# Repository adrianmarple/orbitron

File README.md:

# Basics

Lumatron is a LED sculpture system. You are free to play with this code, but as per the license you may not make money from it.

## TL;DR
```
       ┌──────────────┐  ┌──────────────┐  ┌──────────────┐
       │  Controller  │  │    Admin     │  │   Emulator   │
       │   (browser)  │  │   (browser)  │  │   (browser)  │
       └──────┬───────┘  └──────┬───────┘  └──────┬───────┘
              │ WSS :7777       │ HTTPS           │ WSS
              ▼                 ▼                 ▼
       ┌──────────────────────────────────────────────────┐
       │             Relay server (HTTPS + WSS)           │
       │           e.g. my.lumatron.art / localhost       │
       └──────┬─────────────────┬─────────────────────────┘
              │                 │                   ▲
              │ WSS             │ WSS (out)         │
              ▼                 ▼                   │
       ┌──────────────┐  ┌─────────────┐            │ stls
       │ Raspberry Pi │  │   Arduino   │◄─────────┐ │
       │ Node + Py    │◄─│  esp32.ino  │──────────┤ │
       └──────┬───────┘  └────┬────────┘   pixels │ │
              │ drives        │ drives       info │ │
              ▼               ▼                   │ │
       ╔═══════════════════════╗         ┌────────┴─┴────┐
       ║   Physical piece      ║◄────────┤   Creation    │
       ║   (LED sculpture)     ║ designs │ console (dev) │
       ╚═══════════════════════╝         └───────────────┘
```

- Orbs always connect *outbound* to the relay, so they work behind NATs without port forwarding.
- The relay routes controller / admin / emulator messages to the right orb over its open WebSocket, and serves the websites for the controller, admin, and emulator.
- The Creation console is a dev-time tool (port 8000): it designs the physical piece (3D-printable parts) and writes geometry (pixel info and stls) into the repo.
- Each physical piece is driven by exactly one orb (Pi *or* Arduino).
- In dev (`DEV_MODE: true`), a single machine plays all roles: relay, local Pi-style orb, and emulator standing in for a real piece.

## Connecting an existing piece to the internet

Here's how to connect a piece that does not already have an internet connection (if no piece is already connected to the same wifi you're on these instructions can also be viewed by visiting `https://my.lumatron.art`)
- Plug in the Lumatron box into the power source and the box into the piece (do not plug the piece directly into the usb-c wall plug)
- Wait for the box to boot up and the access point pattern (waves eminating from the bottom point) to show (takes a couple minutes for the raspberry pi based boxes)
- Join the wifi named Lumatron-*name*
- (If the captive portal doesn't automatically appear) visit 10.42.0.1 in your browser.
- Enter the wifi name (SSID) and password in the captive portal
- Visit or refresh `https://my.lumatron.art` once the first pixel turns off

## Controlling a piece

- Visit `https://my.lumatron.art`
- (optional) Turn the site into a progressive web app by following the instructions at the bottom of the page

# Using the Emulator

- Clone (optionally fork first) this repo (`git clone https://github.com/adrianmarple/orbitron`) on your local machine (Windows not supported)
- cd to the root of the repo (folder should be named `orbitron`)
- Install node if you haven't already
- Run `scripts/admin_install.sh` (in the `scripts` folder of the newly cloned repo)
- Start the emulator by running `sudo ./startscript.sh`
- Visit `http://localhost:1337` for the controller
- Visit `http://localhost:1337/test/view` for the emulator (which also contains a controller)

## The admin console

- Make sure you've run `./admin_install.sh`
- Ensure the local server (`sudo ./startscript.sh`) is running
- Visit url `http://localhost:1337/admin`
- Follow instructions for entering a master key
- More details in [the admin folder README](admin)

# Designing a new pattern

See [the idlepatterns folder README](idlepatterns)

# Making a new Game

See [the games folder README](games)

# Setting up your own server

- Fork this repo
- Create an ubuntu server, for instance the lumatron.art is currently hosted through [Digital Ocean](https://www.digitalocean.com/)
- Add a domain (or subdomain of an existing domain you control) to the server (this is required to serve over https)
- Wait and make sure the DNS records are in place (i.e. by checking [https://www.whatsmydns.net/](https://www.whatsmydns.net/))
- Open a console into root of your new server
- Clone your forked repo, i.e. `git clone https://github.com/YOUR_GITHUB_NAME/orbitron`
- Run `cd orbitron` then `scripts/server_install.sh` and enter your domain (and eventually email and other certbot prompts)
- Test by visiting `https://your_domain.com` (you should see "No pieces found on the same wifi")

## Connect a piece to your own server

- Arduino
  - Clear entire arduino flash `esptool.py --chip esp32c3 --port /dev/ttyUSB0 erase_flash`
  - Edit arduino/esp32/esp32.ino: find and replace "my.lumatron.art" with your server
  - Install adruino cli if you haven't already: `scripts/arduino_install.sh`
    - Note two github hooks are installed with this script. One runs `scripts/arduino_build.sh` on git push and uploads the compiled firmware to the server
    - The server url is currently hardcoded, so you should edit "arduino_build.sh" to use your own server, if you want to push to your own repo.
  - Upload to the arduino using `scripts/arduino_upload.sh`
- Raspberry pi
  - Request an unlocked SD along with a piece, email adrian@marplebot.com an request it be unlocked remotely, or follow the **Micro SD card setup** instructions below
  - Get local IP address (once the admin console is set up, you'll be able to get the ip address directly from there)
    - MacOS: `sudo nmap -sn $(ipconfig getifaddr en0)/24`
    - Linux: `sudo nmap -sn $(hostname -I | cut -d' ' -f1)/24`
  - `ssh pi@<IP address>` (password `lumatron`) into the piece
  - Change the password by running `passwd`
  - Edit `orbitron/config.js` to add the line `RELAY_HOST: "your-domain-or-ip",` (also remove `ORB_KEY` if it's there)
  - Run `pm2 restart all`
- Test by visiting `https://your_domain.com` again (you should now see the piece)

## The admin console

- Ensure your server is properly set up
- Visit url `https://your-domain.com/admin`
- Enter the masterkey (from `masterkey.txt` from your server's console) as prompted
- I recommend hitting the "Set ORB_KEY" button followed by the "Save config.js" button for all connected orbs (including the server itself - default named "demo")
  - Note: if this button is not visible hit the "config" button first
- Again see [the admin folder README](admin) for more details

## Continuous integration

You can set up pieces so that pushing to github automatically triggers pieces to restart and pull changes:
- Direct a github action to point to your server
- Add `CONTINUOUS_INTEGRATION: true,` to the config of a piece you want to restart on receiving updates

# REST API

Most things the controller can do can also be done over plain HTTP (useful for scripting: Home Assistant, Shortcuts, cron, or any other forms of automation). This includes preferences, saved presets, the timer schedule, and dimming, but omits game inputs. It is served by the server (i.e. `my.lumatron.art`) under `/api/v1`.

`GET /api/v1/orbs` lists the pieces available to you. Every other path is relative to `/api/v1/orbs/<piece>`, where `<piece>` is a piece's name or its alias (e.g. `https://my.lumatron.art/api/v1/orbs/kitchen/prefs`).

| Method | Path | Body | Description |
|---|---|---|---|
| `GET` | `/prefs` | — | All current settings (pattern, colors, brightness) |
| `PATCH` | `/prefs` | `{"<key>": value, ...}` | Change one or more settings, leaving the rest alone |
| `DELETE` | `/prefs` | — | Reset all settings back to defaults |
| `POST` | `/dim` | — | Step brightness, the same as the hardware button |
| `GET` | `/presets` | — | Saved preset names, which one is current, and cycle membership |
| `PUT` | `/presets/<name>` | — | Save the current settings as `<name>` |
| `POST` | `/presets/<name>/load` | — | Switch to `<name>` |
| `DELETE` | `/presets/<name>` | — | Delete `<name>` |
| `POST` | `/presets/<name>/copy` | `{"copyName": "..."}` | Copy `<name>` to a new preset |
| `POST` | `/presets/<name>/rename` | `{"newName": "..."}` | Rename `<name>` |
| `POST` | `/presets/<name>/reorder` | `{"targetName": "..."}` | Move `<name>` in front of `targetName` |
| `POST` | `/presets/cycle` | — | Advance to the next preset in the cycle |
| `GET` | `/schedule` | — | Timer settings, plus the daily and weekly schedules |
| `PUT` | `/schedule` | `{"useTimer": true, "schedule": [...]}` | Update timer settings |
| `GET` | `/state` | — | All of the above at once |

Preset names may contain spaces, so URL-encode them (`/presets/Evening%20Glow/load`).

A few things worth knowing:
- There's no authentication by default, which is the same as the controller — anyone who knows a piece's name can already control it. To lock it down, add `REST_API_KEY: "some-secret",` to your server's `config.js` and send `Authorization: Bearer some-secret` with every request.
- `GET /api/v1/orbs` only lists pieces on the same wifi as whoever is asking, so the whole fleet isn't enumerable.
- The API connects to a piece the same way a controller does, but without claiming one of the six player slots, so it won't interfere with games or with anyone using the controller. Changes made either way show up in the other immediately.

See [API.md](API.md) for the full endpoint reference.

# Contributions Welcome

Here's a list of things I would welcome receiving PRs for.

- New idle patterns — See [idlepatterns/README.md](idlepatterns/README.md) for details
- New games — See [games/README.md](games/README.md) for details
- Clarifications or other improvements to any READMEs
- UX improvements or other quality of life features for the controller
- General optimizations or improvements

# Arduino setup
Requires a Xiao esp32c3, esp32c6, or esp32s3
- Run `scripts/arduino_install.sh`
- Plug into your computer
- Run `scripts/arduino_upload.sh` to compile and upload to your arduino
- For the first time after installing, check for an access point and add a wifi connection

# Raspberry Pi setup

- Download [an unlocked SD card image](https://www.dropbox.com/scl/fi/ce7uv4ptdwy640emwvc8e/lumatron.zip) from dropbox
- Burn to SD card using `dd` or [Balena Etcher](https://etcher.balena.io/)
- Using `dd`
  - Update `/dev/disk4` or `/dev/sda` below with the correct drive as determined from `diskutil list` or `lsblk` on Linux
  - `diskutil unmountDisk /dev/disk4` or `sudo umount /dev/sda1 && sudo umount /dev/sda2` on Linux
  - go to Download directory or wherever the SD image download is
  - `sudo dd if=lumatron.img of=/dev/disk4 status=progress`
  - On MacOS use `gdd` instead
    - Install with `brew install coreutils`
    - `sudo gdd if=lumatron.img of=/dev/disk4 status=progress`
- Insert SD card into raspberry pi and power on
- Connect via `ssh pi@<<IP_ADDRESS>>` password `lumatron`
- Change to your own password

## (alternative) Fresh Setup

### Image an SD card

- Download Raspberry Pi Imager: https://www.raspberrypi.org/software/
- Select the latest 64-bit Raspberry PI OS
- Click the gear icon to change the settings of the install
- Set hostname to `orbitron`
- Enable SSH with password authentication
- enter pi as the username and enter a password
- Configure wireless LAN to connect to your local wifi
- Set timezone and select us Keyboard layout
- Save and click `WRITE` to burn the image
- Plug SD Card into PI

### Getting connected

- Connect PI to monitor/TV via HDMI cable
- Connect USB keyboard to PI as well
- Power on the PI
- Wait for some time, it may need to reboot 2 or more times
- You should see `orbitron login:` when it is ready
- Login with the username and password you set

### Install git

- `sudo apt install git`

### Clone Repo and run installer

- `git clone https://github.com/adrianmarple/orbitron`
- `~/orbitron/scripts/pi_install.sh`

# Additional useful things of note

## Ripping a new SD card version
- Update `/dev/disk4` below with the correct drive as determined from `diskutil list` or `lsblk`
- `sudo dd if=/dev/disk4 of=lumatron.img bs=8M count=820 status=progress`
- On MacOS use `gdd` instead
  - Install with `brew install coreutils`
  - `sudo gdd if=/dev/disk4 of=lumatron.img bs=8M count=820 status=progress`

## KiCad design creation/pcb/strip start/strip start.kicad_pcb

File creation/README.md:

Here be dragons. Contact adrian@marplebot.com for more details.

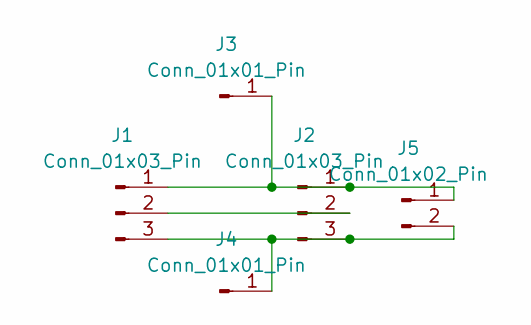
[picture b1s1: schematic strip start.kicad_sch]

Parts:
J1, J2: Conn_01x03_Pin; SolderWirePad_1x01_SMD_1x2mm
J3, J4: Conn_01x01_Pin; SolderWirePad_1x01_SMD_1x2mm
J5: Conn_01x02_Pin; SolderWirePad_1x01_SMD_1x2mm

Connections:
unnamed: J1.1, J2.1, J3.1, J5.1
unnamed: J1.2, J2.2
unnamed: J1.3, J2.3, J4.1, J5.2

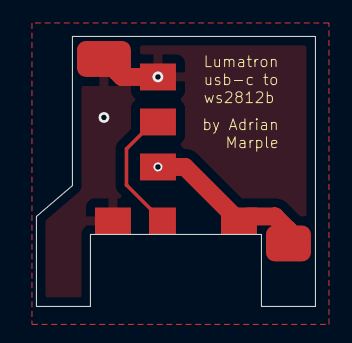
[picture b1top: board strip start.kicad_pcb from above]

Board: 2 copper layers, 15.5 x 15.0 mm, 5 parts (0 on the bottom side), 3 nets.

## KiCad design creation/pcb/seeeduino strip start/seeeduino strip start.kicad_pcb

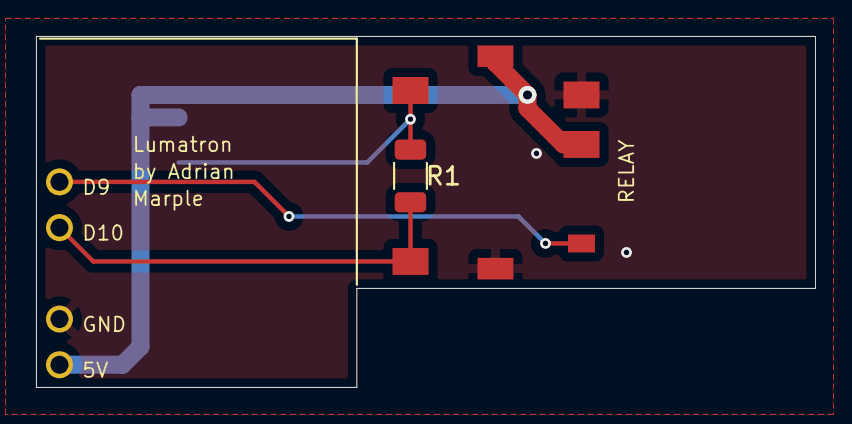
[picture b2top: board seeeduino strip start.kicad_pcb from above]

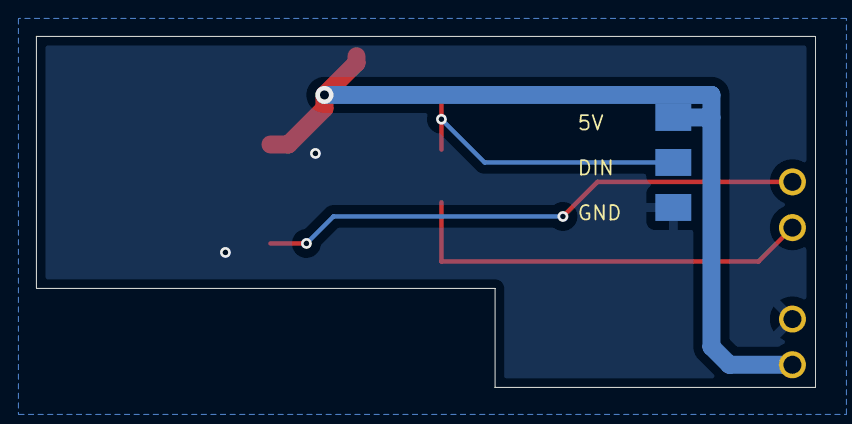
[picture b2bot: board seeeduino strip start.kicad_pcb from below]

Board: 2 copper layers, 43.3 x 19.5 mm, 15 parts (3 on the bottom side), 5 nets.

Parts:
H1, H2, H3, H4: Conn_01x01_Pin
J1, J2, J3, J4, J5, J6, J7, J8, J9, J10: Conn_01x01_Pin
R1: R; R_1206_3216Metric

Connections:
5V: H1.1, J3.1, J4.1, J6.1
D10: H3.1, J10.1, R1.2
DATA: J2.1, J9.1, R1.1
GND: H2.1, J1.1, J5.1, J7.1
RLY: H4.1, J8.1

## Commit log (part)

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2025-08-28 Correction for iframe in lumatron.art home page.
2025-08-28 Correct stl demo orientation and better default pattern. Star designs.
2025-08-29 Corrented radial waves direction and added toggle to reverse.
2025-08-29 New star iteration and fixed some related minor bugs.
2025-09-10 Properly null out ws for an orb when destroyed.
2025-09-30 Revert change I thought was innoculous.
2025-10-07 Better necklace stl. Reset registration button.
2025-10-22 Little bit of logging to understand prefs not loading. Updates to neo-orbitron bits.
2025-10-27 Changed archimedean topologies to not be walls.
2025-10-27 Only use vertex.coordinates during render.
2025-10-27 Better (over)scrolling behavior.
2025-10-29 Removed no longer used conversion code from prefs.py
2025-10-29 Another logging tweak to help find pref.json dropping bug.
2025-10-30 Add wifi script. Always gen key after making a random orbID.
2025-10-31 No more eninge.UP.
2025-11-01 Varius game improvements.
2025-11-15 Power calibration system and related improvements.
2025-11-15 More calibration system refinements.
2025-11-16 Revamp of old dodec hamiltonian cycle.
2025-11-18 NO_LOCAL_REGISTRATION config option.
2025-11-18 Various edge case improvements for saved prefs.
2025-11-19 remove 0 from wlan0 in wifi hotspot startup
2025-11-19 Some anti-race-condition measures in prefs.py.
2025-11-19 Trying to avoid blip when toggling useTimer back and forth.
2025-11-19 Check for idempotent pref changes.
2025-11-19 Restoring backups retooled to handle large files.
2025-11-19 Able to log falsy values.
2025-11-19 Correction.
2025-11-20 Slightly better behavior for turning dimmer on automatically.
2025-11-24 Reinforcer for vertical pipe connection.
2025-11-27 Pendant box.
2025-11-29 Another bug fix attempt, plus some cleanup.
2025-12-02 Line data.
2025-12-03 Multimiter likely actually working.
2025-12-03 Getting octahedron set up for finalization.
2025-12-03 Corrections for negative area and octpure rotation.
2025-12-05 Corrected dedeccycle orientation.
2025-12-06 Don't save empty prefs + pipe jammer.
2025-12-07 Updating greatrhomb.
2025-12-08 Incorporated game feelback from MADE session.
2025-12-09 Remote input correction.
2025-12-09 Remote input correction 2.
2025-12-09 Remote input correction 4.
2025-12-09 Remote input correction 6.
2025-12-09 Remote input correction 7.
2025-12-10 Some instructions around power calibration.
2025-12-12 Some fixes to nextEdge. Plus hacky version of face channel for octpure.
2025-12-16 Tetra pure and correction to basis creation.
2025-12-23 Important saving bug fix. Plus starting work on tricolor color option.
2025-12-29 Finished up strong edges and staff update.
2025-12-29 Fixed and improved speedbumps.
2025-12-30 Added lines to butterfly to be able to print new version of usb-c port wall.
2026-01-15 More improvements to LED supports.
2026-01-26 Octtrue.
2026-01-31 Tested on pi and corrected.
2026-02-03 Backup python restart. More iteration on lamp interface.
2026-02-04 Auto detect pin threshold.
2026-02-05 More pin calibration.
2026-02-05 Shorted spurious trigger time.
2026-02-09 Hot fix.
2026-02-10 Prefer doubling back in pathing.
2026-02-10 Better logging for cycling.
2026-02-10 More prefs logging.
2026-02-10 Different approach to pin action detection.
2026-02-11 Try windowing for pin comparison.
2026-02-11 Avoid initial start trigger
2026-02-11 Small logging change.
2026-02-11 More calibration.
2026-02-16 Restore prefs.save.
2026-02-16 Prefs save hotfix.
2026-02-17 Another capacitive touch calibration attempt.
2026-02-25 Starting to mess with Claude Code.
2026-02-25 Made landing page orbs reorderable via drag and drop.
2026-02-25 Don't send game info if not game is playing.
2026-02-26 Lining up emulator correctly.
2026-02-27 Added skipped projects to bottom in separate list.
2026-02-27 Line topology pattern.
2026-02-27 Check against all backups not just most recent.
2026-02-27 Fixed parts rendering.
2026-02-27 Auto generate arduino files.
2026-02-28 Added all major patterns to arduino code, and refined.
2026-03-05 Experimenting with corner sleeves.
2026-03-05 Some controller optimizations.
2026-03-05 Potential fix for stls not animating.
2026-03-05 Using on orb connection status for better reactivity.
2026-03-14 Changed integrated USB-C port to allow for new pcb.
2026-03-14 Renamed laser.js
2026-03-14 Swapped x and y coords in rhombicosidodecahedron.json
2026-03-16 Additional improvements to scrolling in registation home page.
2026-03-16 Moved game related code out of controller.js/html
2026-03-16 Removed unused websocket python lib.
2026-03-16 Starting to separate admin and creation consoles.
2026-03-16 More refinements of new admin site.
2026-03-16 Final changes before sending new admin site to server.
2026-03-17 Changed how SKIP works.
2026-03-17 Dry run of frest server install. Hot fix 2.
2026-03-17 Dry run of frest server install. Hot fix 3.
2026-03-17 Dry run of frest server install. Hot fix 5.
2026-03-18 More README improvements and tested fresh local install.
2026-03-19 Various small improvements while testing server setup.
2026-03-19 Server testing wrap up.
2026-03-21 Setting up snake piece generation.
2026-03-21 Snake going 3D (to start)
2026-03-24 Removed multisampling pins each frame.
2026-03-25 Changed shortcut icon.
2026-03-25 Image change to be actual share image as intended.
2026-03-26 Edge case for controller and improvements and cleanup in stl creation.
2026-03-26 Don't cache temp orb info.
2026-03-26 Snake git files.
2026-03-26 Cleanup for writing to pixels, plus speculative option for apa102 strip.
2026-03-26 Forward looking APA102 optimization.
2026-03-26 Correction to optimization.
2026-03-27 Made socket scope of orbToRelay socket local where appropriate
2026-03-31 Better calculations in list of orbs.
2026-04-08 Working on wifi enabled arduino. Need to make a change to admin.
2026-04-08 Arduino working with controller./deploy.sh
2026-04-09 Split arduino code up. Added timer functionality
2026-04-09 Arduino: backup system, timing prefs, security, and relay fixes.
    - Precomputed nextBackupMs for 2am auto-backup (same pattern as nextEventMs)
    - Added backup/restore system with LittleFS savedprefs directory
    - One-off migration for camelCase → ALL_CAPS config keys
    - Fixed JsonPairConst error in handleRestoreFromBackup
    - Skip geometry fetch when PIXELS is empty or "null"
    - Move WebSocket init before geometry load so admin commands always work
2026-04-09 Reapply "Arduino: backup system, timing prefs, security, and relay fixes."
    This reverts commit 0cbe4f66541bb5a208b4f94829bfcf041e3859d2.
2026-04-09 Remove one-off camelCase→ALL_CAPS config migration from setup.
2026-04-09 Arduino OTA CI ready for testing.
2026-04-09 Only update arduino firmware if relevant files have updated.
2026-04-10 Can now rotate emulator with touch events.
2026-04-10 More robust arduino update system.
2026-04-10 Added more logging to arduino
2026-04-10 Poll for OTA update after receiving notification that there may be an update
2026-04-11 Trying to get server fireware compilation to work.
2026-04-11 Hopefully, fix server-side arduino compilation errors.
2026-04-11 Another try at arduino compilation.
2026-04-12 Got button working with arduino.
2026-04-12 Fixed Set ORB_KEY for arduino.
2026-04-13 Solidifying.
2026-04-14 Better styling for captive portal.
2026-04-14 Captive portal improvements.
2026-04-14 Final captive portal touches.
2026-04-15 Better access point cleanup.
2026-04-16 Generalize archimedean solid creation include capture walls.
2026-04-17 Printing setup for new desklamp and associated fixes and generalizations.
2026-04-21 Compile arduino firmware locally.
2026-04-21 Improvements to fireware upload system.
2026-04-21 Minor arduino code changes to test fireware upload system.
2026-04-21 Avoid recompiling firmware when unnecessary.
2026-04-21 Setting up for staging server.
2026-04-21 check for secret with github webhook POSTs
2026-04-21 Different logging for github webhooks
2026-04-21 Removed debugging line.
2026-04-21 Minor controller fixes.
2026-04-22 Negated pcb_offset for most cases.
2026-04-23 Actual fix for pcb-offset in middle of foldwalls.
2026-04-23 Reorganized how config info is passed to the controller. Controller button now iminated gestures of main physical button.
2026-04-23 Improvements to command view of admin console.
2026-04-23 Removed zip of logs request. Plus some minor fixes.
2026-04-23 Button to copy preset.
2026-04-23 First attempt at swivelmount
2026-04-24 Saved presets can be reordered now.
2026-04-24 More refinement of swivel mounts.
2026-04-25 Better conversion of pi and arduino backsup to each other.
2026-04-25 Feedback that login code was wrong.
2026-04-26 Fixed greatrhomb's stl
2026-04-27 Prevent power button in home page from opening orb.
2026-04-27 Support for ESP32-C6 and drop support for SAMD20
2026-04-28 Use pref order for advance preset in arduino.
2026-04-28 Config to only attempt to connect to the internet once, then stop trying.
2026-04-28 Fixed firmwareVersions endpoint calls.
2026-04-28 Detect preexisting wifi credentials better for arduino.
2026-04-30 Updated pattern icon.
2026-04-30 New pcb for arduino box. Plus actually saved scad files and organized them a bit.
2026-04-30 Split up construction.js and reduced the reliance on globals.
2026-05-03 Redoing pendant. Plus some index VARIABLE refactoring and other small cleanup.
2026-05-04 Better zero states for no saved prefs plus make sure saved list doesn't go to high with wide aspect ratios.
2026-05-04 Check to prevent orb from becoming inaccessible when saving config.
2026-05-04 Send correct CI message to Pis.
2026-05-04 Dimmer instant button feedback. Plus corrected arduino behavior.
2026-05-06 Advance through all presets in none included in cycles.
2026-05-07 Visual indicator that preset is included in cycles.
2026-05-07 Clean up orphaned python processes.
2026-05-07 Added icosidodectrue git files, plus some bugs fixes found in the process.
2026-05-09 Got s3 chip to work and optimized memory to work with 1200 pixels. Default arduinos to turn dimmer to 1 on power up.
2026-05-09 Default arduino button pins.
2026-05-09 Better handling of dimmer and keep timingPrefs cached in memory.
2026-05-09 Undo network on same core as render.
2026-05-10 Dodectrue topology.
2026-05-11 Avoid network blocking render start
2026-05-11 Special AP rendering
2026-05-11 Fixed scope of priorityToCurrentText.
2026-05-11 Access point visualization itertion.
2026-05-11 Use dvh instead of vh in most instances.
2026-05-12 Eliminated multi button press gestures.
2026-05-15 Abandoning use of ws2812c double density strip.
2026-05-15 Updated dodectrue auto generated git files.
2026-05-18 Figuring out potential large infinite mirror cube.
2026-05-19 Temp removing OTA freeze.
2026-05-19 Actually use custom partition scheme.
2026-06-02 SKIP_AC_ON_POWER defaults to true when remote pin is set
2026-06-02 Avoid redundant currentprefsname.txt writes.
2026-06-02 Arduino kept in sync with controller via state hash heartbeat.
2026-06-03 Flash writes use mutex to avoid interferring with rendering.
2026-06-04 Fixed issues with timer getting started on arduino.
2026-06-05 Fixed various issues with fading and schedule events.
2026-06-05 Make sure button works with still connecting to network.
2026-06-05 Set rem early to avoid console error in controller.
2026-06-06 Place all flash writes/deletes behind the render mutex.
2026-06-06 Avoid fading out/in when schedule presets are the same
2026-06-06 3D vector won't flip on pref update.
2026-06-11 Fixed power calibration for arduino.
2026-06-12 New mount for microbox.
2026-06-12 Show version timestamps in admin.
2026-06-12 Flip fireware build order.
2026-06-13 Arduino to use epoch time for timestamp to be consistent across reboots.
2026-06-13 Broadcast update to connected controllers on relay reconnect/reboot.
2026-06-15 MAX_BRIGHTNESS_OVERRIDE config. Plus default max brightness 150 isntead of 200.
2026-06-26 A couple options for pair of windows piece.
2026-06-27 Fixed one-off emulator interferring with other emulation.
2026-06-27 Two more panes options.
